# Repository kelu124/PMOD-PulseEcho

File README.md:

# PMOD-PulseEcho

* Objective: test two designs for pulser and acquisition boards.
* Might work well with the [FT600 test board](https://github.com/kelu124/ft600) (OSHWA certified)

## Software

### FT600 

* First tries with [FT600, on Kilsyth](software/kilsyth/), some issues. 
* Current tests on ACQ, FIFO seems OK.
* Today: on hold.

### [icebreaker](/software/icebreaker/)

* UP5K board
* Today: tests ongoing. FIFO tests.

### [pico / rp2040](/software/pico/)

* Tests ongoing
* Today: Acq seems OK. Issue with some pins (D6 D7 seem buggy). Migth try with lower frequency.

## Hardware

* First designs done, some mistakes.

* Pulser TODO
  * PMOD pin reversed, to correct
  * Spacing of top pins to respect a 2.54" grid.
  
* Acq TODO
  * Right spacing of PMOD headers
  * Right labelling of pins

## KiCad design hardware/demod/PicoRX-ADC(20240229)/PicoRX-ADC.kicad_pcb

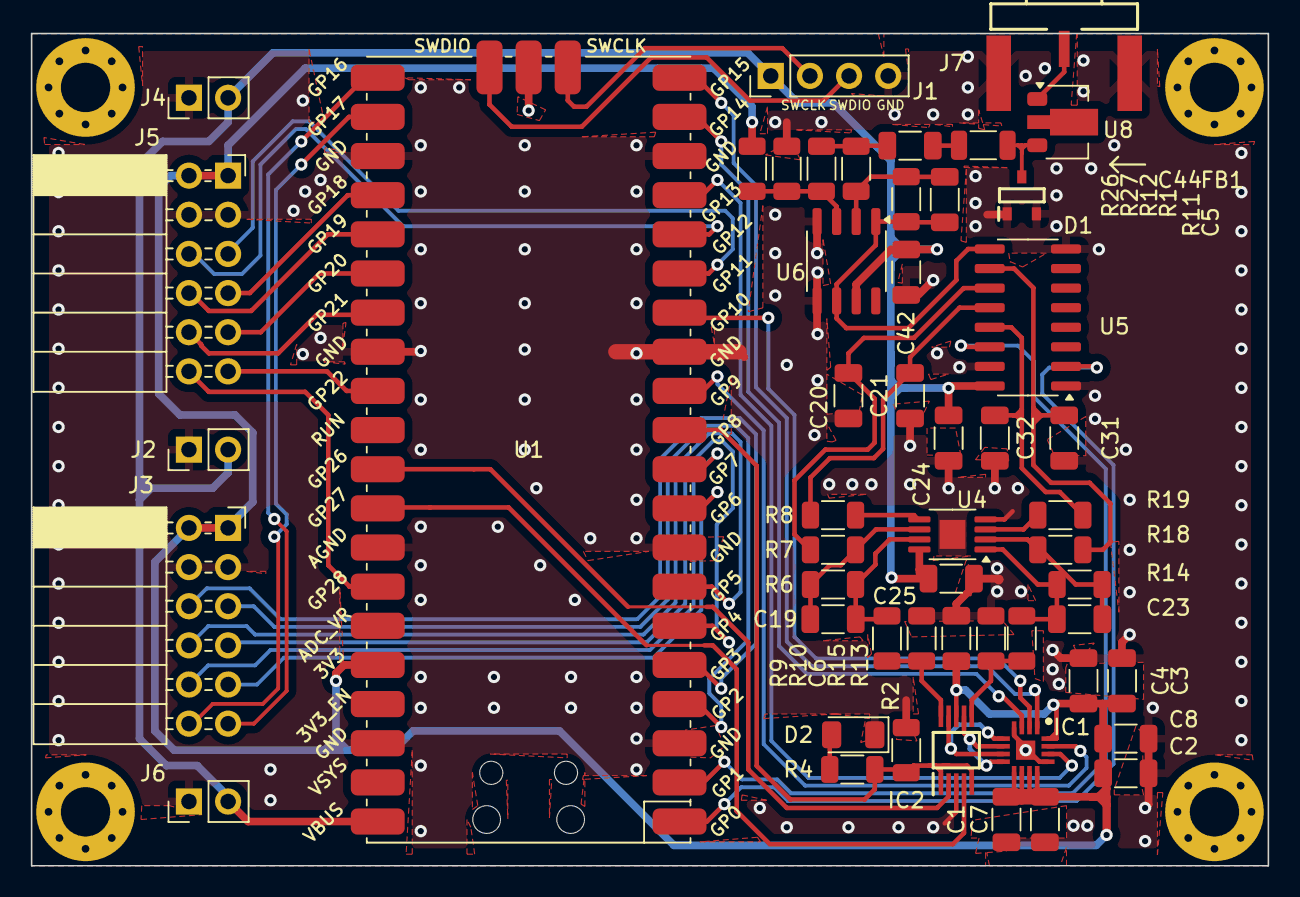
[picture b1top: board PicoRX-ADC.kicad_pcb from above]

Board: 2 copper layers, 80.2 x 54.0 mm, 52 parts (0 on the bottom side), 53 nets.

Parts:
C1, C2, C4, C6: 100nF; C_1206_3216Metric
C3: 4.7uF; C_1206_3216Metric
C5: 22p; C_1206_3216Metric
C7, C8: 10uF; C_1206_3216Metric
C19, C23: 1p; C_1206_3216Metric
C20, C21, C31, C32: 15n; C_1206_3216Metric
C24, C25, C42, C44: 100n; C_1206_3216Metric
D1: BAV99-7-F; SOT95P240X120-3N
D2: LED; LED_1206_3216Metric
FB1: ILHB1206ER750V; L_1206_3216Metric
IC1: MAX11190ATE+T; QFN50P300X300X80-17N
IC2: TS5A23159DGSR; SOP50P490X110-10N
J1: Conn_01x04; PinHeader_1x04_P2.54mm_Vertical
J2, J4, J6: 22-23-2021; PinHeader_1x02_P2.54mm_Vertical
J3, J5: 90122-0126; PinSocket_2x06_P2.54mm_Horizontal
J7: AMPHENOL_132357-11
R1: 50; R_1206_3216Metric
R2: 4.7K; R_1206_3216Metric
R4: 1K; R_1206_3216Metric
R6, R14: 100k; R_1206_3216Metric
R7, R8, R18, R19: 100; R_1206_3216Metric
R9, R13: 470; R_1206_3216Metric
R10, R15: 1k; R_1206_3216Metric
R11: 220; R_1206_3216Metric
R12: 0; R_1206_3216Metric
R26, R27: 10K; R_1206_3216Metric
U1: Pico; RPi_Pico_SMD
U4: LTC6227; MSOP-8-1EP_3x3mm_P0.65mm_EP1.68x1.88mm
U5: FST3253; SOIC-16_3.9x9.9mm_P1.27mm
U6: LTC6226xS8; SO-8_3.9x4.9mm_P1.27mm
U8: MD0100N8-G; SOT-89-3

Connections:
+3.3V: C1.2, C2.2, C3.2, C4.2, C6.2, C7.2, C8.2, IC1.9 (REFA), IC1.10 (REFB), IC1.11 (VDD_1), IC1.12 (VDD_2), IC1.16 (OVDD), IC2.8 (VCC), J3.1, J3.2, J5.1, J5.2, R26.1, U1.36 (3V3)
+5V: C24.1, C25.1, C42.1, J1.1, J2.2, J4.2, J6.2, U1.40 (VBUS), U4.8 (V+), U5.16 (VCC), U6.7 (V+)
ADC_RX_I: IC1.5 (AIN1A), IC1.7 (AIN2A), IC2.9 (NC1)
ADC_RX_Q: IC1.6 (AIN1B), IC1.8 (AIN2B), IC2.7 (NC2)
CHSEL: IC1.15 (CHSEL), U1.12 (GPIO9)
GND: C1.1, C2.1, C3.1, C4.1, C6.1, C7.1, C8.1, C20.1, C21.1, C24.2, C25.2, C31.1, C32.1, C42.2, D1.1, D1.2, D2.1 (K), IC1.4 (GND_1), IC1.13 (GND_2), IC1.17 (EP), IC2.3 (GND), J1.4, J2.1, J3.3, J3.4, J4.1, J5.3, J5.4, J6.1, J7.2, R2.1, R10.1, R15.1, R27.2, U1.3 (GND), U1.8 (GND), U1.13 (GND), U1.18 (GND), U1.23 (GND), U1.28 (GND), U1.33 (AGND), U1.38 (GND), U1.42 (GND), U4.4 (V-), U4.9, U5.1 (1~OE), U5.8 (GND), U5.15 (2~OE), U6.4 (V-), U6.5 (V-)
GPIO2: J3.5, U1.4 (GPIO2)
GPIO3: J3.6, U1.5 (GPIO3)
GPIO4: J3.7, U1.6 (GPIO4)
GPIO5: J3.8, U1.7 (GPIO5)
GPIO6: J3.9, U1.9 (GPIO6)
GPIO7: J3.10, U1.10 (GPIO7)
GPIO11: J5.5, U1.15 (GPIO11)
GPIO12: J5.6, U1.16 (GPIO12)
GPIO16: J3.11, U1.21 (GPIO16)
GPIO17: J3.12, U1.22 (GPIO17)
GPIO18: J5.7, U1.24 (GPIO18)
GPIO19: J5.8, U1.25 (GPIO19)
GPIO20: J5.9, U1.26 (GPIO20)
GPIO21: J5.10, U1.27 (GPIO21)
GPIO22: J5.11, U1.29 (GPIO22)
GPIO28: J5.12, U1.34 (GPIO28_ADC2)
IN_CH: IC2.1 (IN1), IC2.5 (IN2), R2.2, R4.2, U1.11 (GPIO8)
LO_I: U1.2 (GPIO1), U5.14 (S0)
LO_Q: U1.1 (GPIO0), U5.2 (S1)
unnamed: C19.2, R6.2, R9.1, U4.7
unnamed: C23.2, R13.1, R14.2, U4.1
unnamed: C44.1, R1.1, R12.2
unnamed: C44.2, FB1.2
unnamed: D2.2 (A), R4.1
unnamed: R19.1, U4.3 (+)
unnamed: C23.1, R14.1, R18.1, U4.2 (-)
unnamed: R8.1, U4.5 (+)
unnamed: C19.1, R6.1, R7.1, U4.6 (-)
unnamed: C31.2, R18.2, U5.10 (2B1)
unnamed: C20.2, R7.2, U5.11 (2B2)
unnamed: C21.2, R8.2, U5.12 (2B3)
unnamed: C32.2, R19.2, U5.13 (2B4)
unnamed: R12.1, R26.2, R27.1, U6.3 (+)
unnamed: C5.1, R1.2, R11.1, U6.2 (-)
unnamed: J7.1, U8.1 (A)
unnamed: D1.3, FB1.1, U8.3 (B)
PICO_RX_I: IC2.2 (NO1), U1.31 (GPIO26_ADC0)
PICO_RX_Q: IC2.4 (NO2), U1.32 (GPIO27_ADC1)
RF_PREAMP: C5.2, R11.2, U5.9 (2A), U6.1 (FB), U6.6
RX_I: IC2.10 (COM1), R9.2, R10.2
RX_Q: IC2.6 (COM2), R13.2, R15.2
SCLK: IC1.3 (SCLK), U1.19 (GPIO14)
SDATA_A: IC1.1 (DOUTA), U1.20 (GPIO15)
SDATA_B: IC1.2 (DOUTB), U1.14 (GPIO10)
SWCLK: J1.2, U1.41 (SWCLK)
SWDIO: J1.3, U1.43 (SWDIO)
~CS: IC1.14 (~CS), U1.17 (GPIO13)

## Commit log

2024-01-27 Adding tests
2024-01-27 Cleanup
2024-01-27 Update pico
2024-01-27 adding ftd2xx
2024-01-27 Tests on icebreaker
2024-01-27 Adding fifo
2024-01-29 Prepping for pico-ice
2024-01-29 Test v1
